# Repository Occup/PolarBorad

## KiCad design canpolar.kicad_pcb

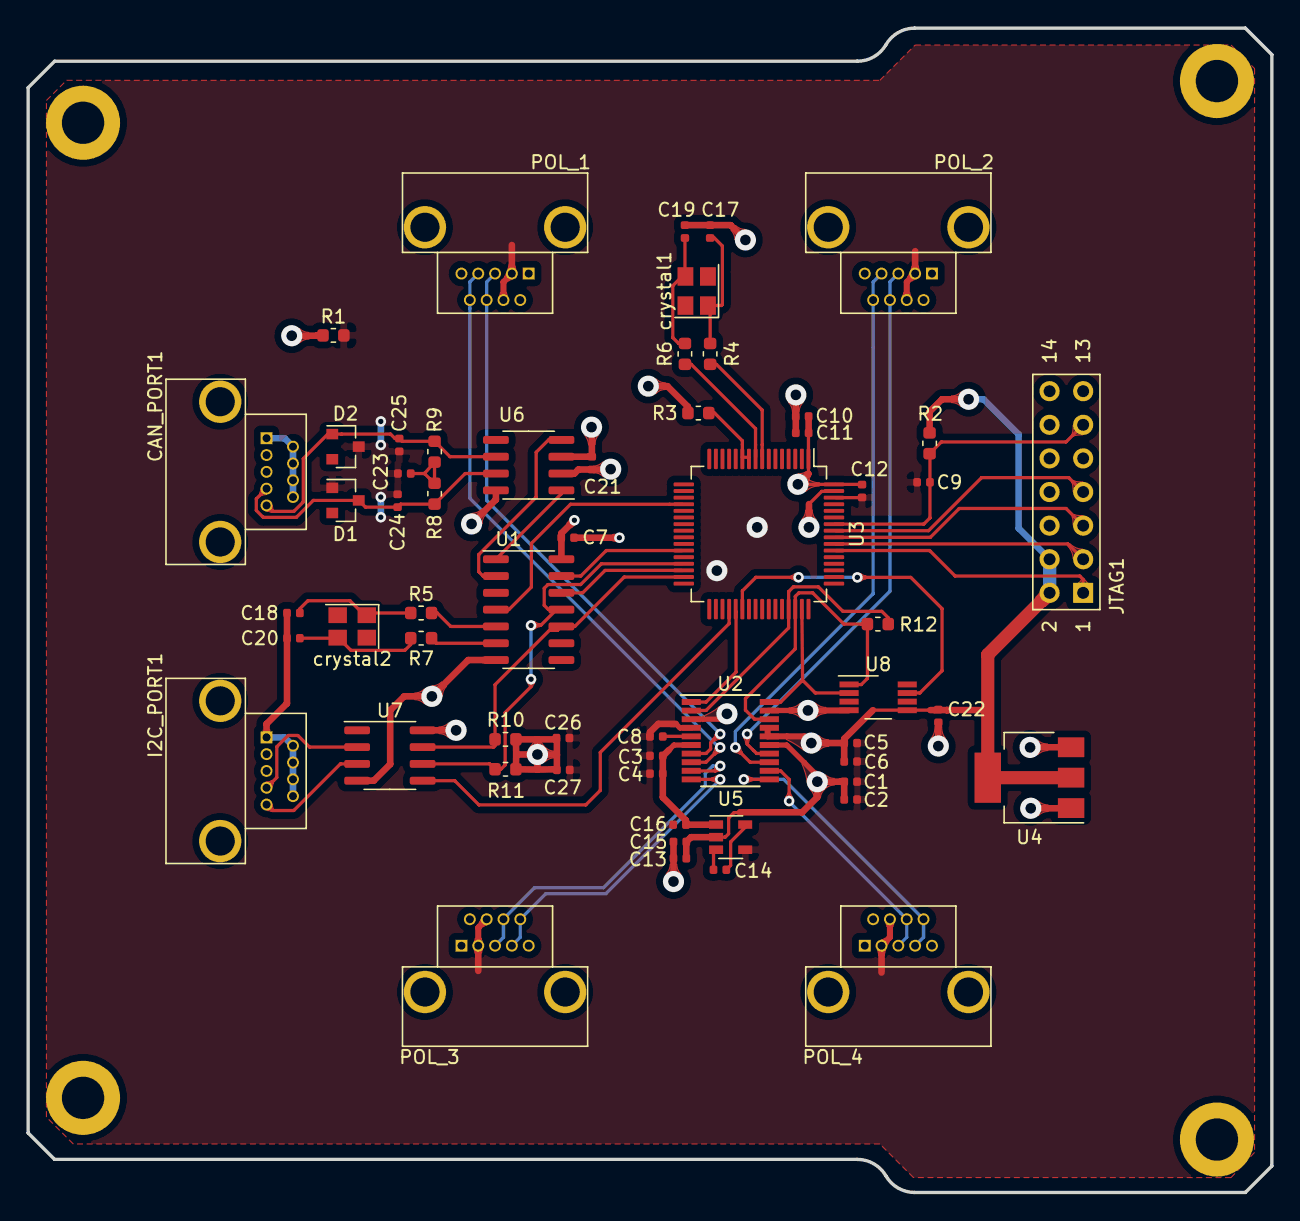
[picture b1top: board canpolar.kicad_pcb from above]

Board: 4 copper layers, 94.0 x 88.0 mm, 62 parts (0 on the bottom side), 48 nets.

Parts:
C1, C3, C6, C11, C15, C26: 10uF; C_0402_1005Metric
C2, C4, C5, C7, C9, C10, C12, C13, C21, C22, C27: 0.1uF; C_0402_1005Metric
C8: 680nF; C_0402_1005Metric
C14, C16: 1uF; C_0402_1005Metric
C17, C18, C19, C20: 12pF; C_0402_1005Metric
C23: 4700pF; C_0402_1005Metric
C24, C25: 47pF; C_0402_1005Metric
CAN_PORT1: P_COM_CAN; header-9
D1, D2: D_Zener_Small; D_SOT-23_ANK
I2C_PORT1: P_COM_IIC; header-9
JTAG1: JTAG14PinConn; JTAG14
O1, O2, O3, O4: Hole; PadCorner
POL_1: POL_1; header-9
POL_2: POL_2; header-9
POL_3: POL_3; header-9
POL_4: POL_4; header-9
R1, R3, R4, R5, R6, R7: 0K; R_0603_1608Metric
R2: 47K; R_0603_1608Metric
R8, R9: 60.4; R_0603_1608Metric
R10, R11: 2.2K; R_0603_1608Metric
R12: 10K; R_0603_1608Metric
U1: MCP2517FD-xSL; SOIC-14_3.9x8.7mm_P1.27mm
U2: AD7328BRUZ; TSSOP-20_4.4x6.5mm_P0.65mm
U3: MSP430F1611; LQFP-64_10x10mm_P0.5mm
U4: AMS1117-3.3; SOT-223-3_TabPin2
U5: TPS60401DBVT; SOT-23-5
U6: SN65HVD230; SOIC-8_3.9x4.9mm_P1.27mm
U7: PCA9515AD; SOIC-8_3.9x4.9mm_P1.27mm
U8: LM70CIMM-3; VSSOP-8_3.0x3.0mm_P0.65mm
crystal1: 6M; Crystal_SMD_3225-4Pin_3.2x2.5mm
crystal2: 40M; Crystal_SMD_3225-4Pin_3.2x2.5mm

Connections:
6Min: R4.2, U3.8
6Mout: R6.2, U3.9
40Min: R5.2, U1.5
40Mout: R7.2, U1.6
#RST: C9.2, JTAG1.11, R2.2, U3.58
+3V3: C5.2, C6.2, C7.1, C10.2, C11.2, C12.2, C21.1, C22.1, C26.1, C27.1, JTAG1.2, JTAG1.4, R2.1, R10.1, R11.1, U1.14, U2.16, U2.17, U3.1, U3.64, U4.2, U6.3, U7.8, U8.5
+5V: C1.2, C2.2, C13.2, C15.2, CAN_PORT1.2, CAN_PORT1.3, I2C_PORT1.2, I2C_PORT1.3, POL_1.1, POL_1.6, POL_2.1, POL_2.6, POL_3.1, POL_3.6, POL_4.1, POL_4.6, U2.15, U4.3, U5.2
-5V: C3.2, C4.2, C16.2, U2.6, U5.1
/CANH: C24.1, CAN_PORT1.4, D1.1, R8.2, U6.7
/CANL: C25.2, CAN_PORT1.5, D2.2, R9.1, U6.6
/SCL: I2C_PORT1.4, U7.2
/SDA: I2C_PORT1.5, U7.3
ADC_EN: U2.1, U3.37
CAN_COM: U1.13, U3.27
CHN0: POL_1.3, POL_1.8, U2.7
CHN1: POL_1.4, POL_1.9, U2.8
CHN2: POL_2.3, POL_2.8, U2.14
CHN3: POL_2.4, POL_2.9, U2.13
CHN4: POL_3.3, POL_3.8, U2.9
CHN5: POL_3.4, POL_3.9, U2.10
CHN6: POL_4.3, POL_4.8, U2.12
CHN7: POL_4.4, POL_4.9, U2.11
GNDA: C1.1, C2.1, C3.1, C4.1, C5.1, C6.1, C8.1, C9.1, C12.1, C16.1, C23.2, C24.2, C25.1, C26.2, C27.2, D1.2, D2.1, POL_1.2, POL_1.7, POL_2.2, POL_2.7, POL_3.2, POL_3.7, POL_4.2, POL_4.7, R1.2, U2.4, U3.62, U5.4
GNDD: C7.2, C10.1, C11.1, C13.1, C15.1, C17.1, C18.1, C19.1, C20.1, C21.2, C22.2, CAN_PORT1.1, CAN_PORT1.6, CAN_PORT1.7, CAN_PORT1.8, CAN_PORT1.9, I2C_PORT1.1, I2C_PORT1.6, I2C_PORT1.7, I2C_PORT1.8, I2C_PORT1.9, JTAG1.9, R1.1, R3.2, U1.7, U2.3, U2.19, U3.63, U4.1, U6.2, U6.8, U7.4, U8.4
IIC_EN: U3.36, U7.5
INT: U1.4, U3.20
unnamed: C8.2, U2.5
unnamed: C14.1, U5.3
unnamed: C14.2, U5.5
unnamed: C17.2, R4.1, crystal1.1
unnamed: C18.2, R5.1, crystal2.1
unnamed: C19.2, R6.1, crystal1.3
unnamed: C20.2, R7.1, crystal2.3
unnamed: C23.1, R8.1, R9.2
unnamed: R3.1, U3.10, U3.11
RXCAN: U1.2, U6.4
SCL1_UCLK0: R10.2, U1.10, U3.31, U7.7
SDA1_SIMO0: R11.2, U1.11, U3.29, U7.6
SIMO1: R12.1, U2.2, U3.45
SOMI0: U1.12, U3.30
SOMI1: R12.2, U2.18, U3.46, U8.1
TCK: JTAG1.7, U3.57
TDI\TCK: JTAG1.3, U3.55
TDO\TDI: JTAG1.1, U3.54
TEMPMEA: U3.38, U8.7
TMS: JTAG1.5, U3.56
TXCAN: U1.1, U6.1
UCLK1: U2.20, U3.47, U8.2
